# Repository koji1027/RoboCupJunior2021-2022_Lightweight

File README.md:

# RoboCupJunior2023_Lightweight
 高崎高校物理部 ロボカップジュニア2023 ライトウェイト部門

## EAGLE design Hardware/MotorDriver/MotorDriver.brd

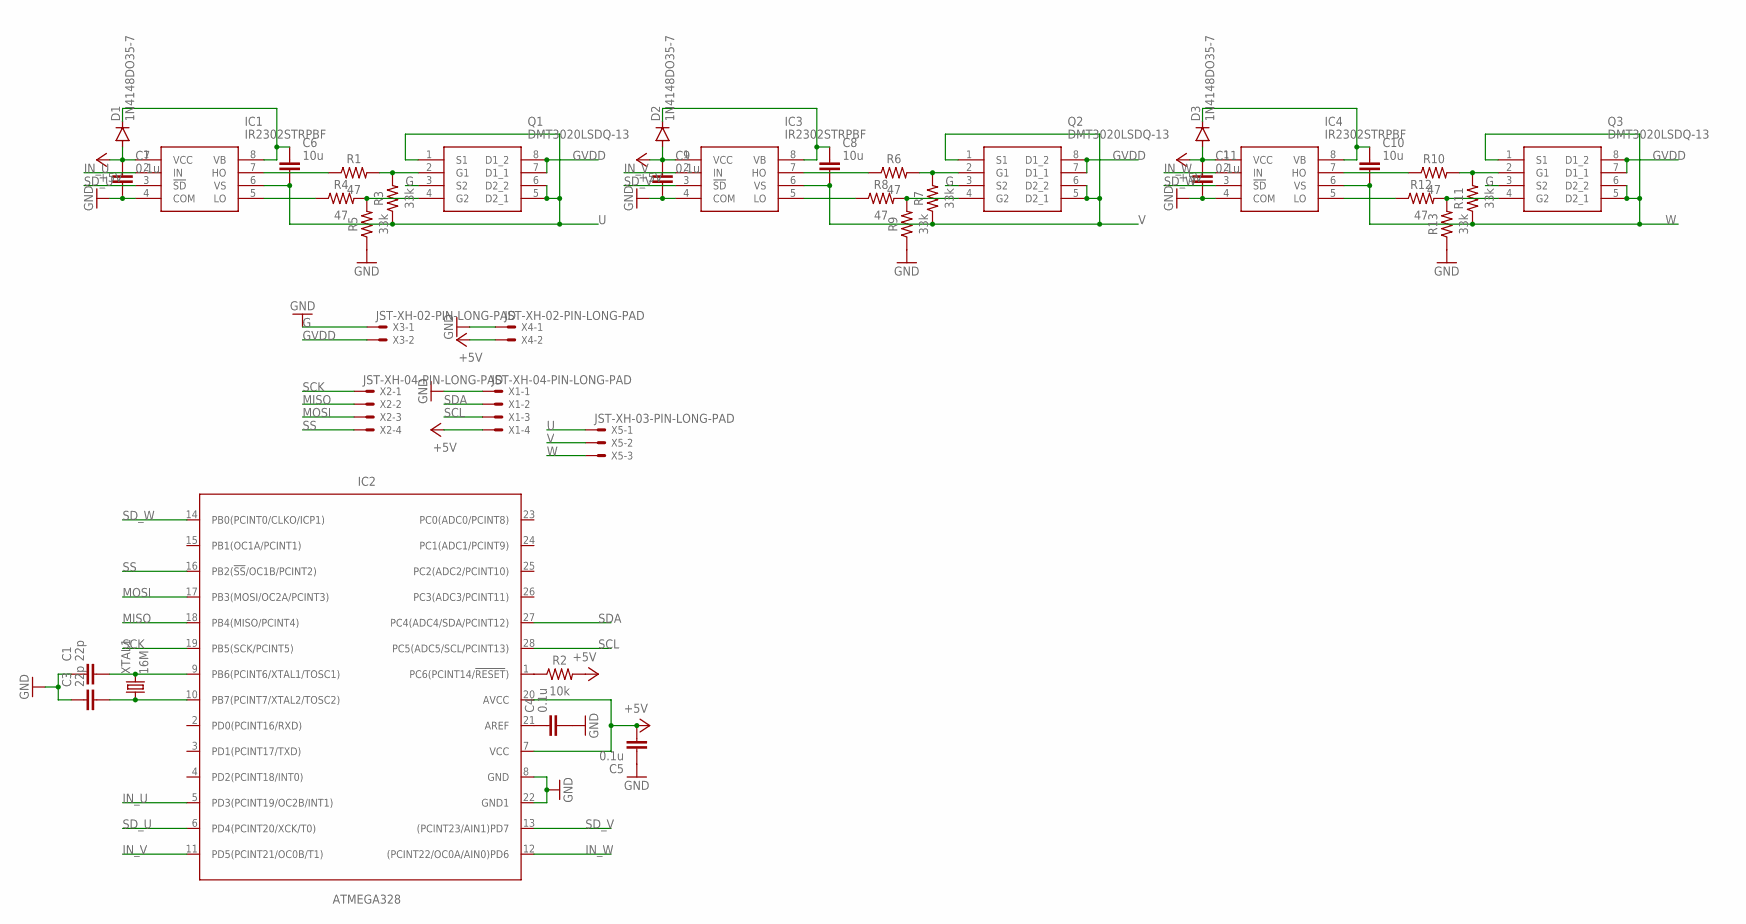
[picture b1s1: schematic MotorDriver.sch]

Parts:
C1, C3: 22p; CAPC1608X85
C4, C5, C7, C9, C11: 0.1u; CAPC1608X85
C6, C8, C10: 10u; CAPC1608X85
D1, D2, D3: 1N4148DO35-7; DO35-7
IC1, IC3, IC4: IR2302STRPBF; SOIC127P600X175-8N
IC2: ATMEGA328; DIP1016W53P254L3467H457Q28B
Q1, Q2, Q3: DMT3020LSDQ-13; SOIC127P600X170-8N
R1, R4, R6, R8, R10, R12: 47; RESC1608X60
R2: 10k; RESC1608X60
R3, R5, R7, R9, R11, R13: 33k; RESC1608X60
X1, X2: JST-XH-04-PIN-LONG-PAD; JST-XH-04-PACKAGE-LONG-PAD
X3, X4: JST-XH-02-PIN-LONG-PAD; JST-XH-02-PACKAGE-LONG-PAD
X5: JST-XH-03-PIN-LONG-PAD; JST-XH-03-PACKAGE-LONG-PAD
XTAL1: 16M; XTALRR488W45L1150T500H350B

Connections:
+5V: C5.2, C7.1, C9.1, C11.1, D1.A, D2.A, D3.A, IC1.1 (VCC), IC2.7 (VCC), IC2.20 (AVCC), IC3.1 (VCC), IC4.1 (VCC), R2.2, X1.4, X4.2
G: Q1.3 (S2), Q2.3 (S2), Q3.3 (S2), X3.1
GND: C1.1, C3.1, C4.2, C5.1, C7.2, C9.2, C11.2, IC1.4 (COM), IC2.8 (GND), IC2.22 (GND1), IC3.4 (COM), IC4.4 (COM), R5.1, R9.1, R13.1, X1.1, X4.1
GVDD: Q1.7 (D1_1), Q1.8 (D1_2), Q2.7 (D1_1), Q2.8 (D1_2), Q3.7 (D1_1), Q3.8 (D1_2), X3.2
IN_U: IC1.2 (IN), IC2.5 (PD3(PCINT19/OC2B/INT1))
IN_V: IC2.11 (PD5(PCINT21/OC0B/T1)), IC3.2 (IN)
IN_W: IC2.12 ((PCINT22/OC0A/AIN0)PD6), IC4.2 (IN)
MISO: IC2.18 (PB4(MISO/PCINT4)), X2.2
MOSI: IC2.17 (PB3(MOSI/OC2A/PCINT3)), X2.3
unnamed: C1.2, IC2.9 (PB6(PCINT6/XTAL1/TOSC1)), XTAL1.2
unnamed: C3.2, IC2.10 (PB7(PCINT7/XTAL2/TOSC2)), XTAL1.1
unnamed: IC2.1 (PC6(PCINT14/!RESET!)), R2.1
unnamed: C4.1, IC2.21 (AREF)
unnamed: C6.1, D1.C, IC1.8 (VB)
unnamed: IC1.7 (HO), R1.1
unnamed: Q1.2 (G1), R1.2, R3.2
unnamed: Q1.4 (G2), R4.2, R5.2
unnamed: IC1.5 (LO), R4.1
unnamed: C8.1, D2.C, IC3.8 (VB)
unnamed: IC3.7 (HO), R6.1
unnamed: Q2.2 (G1), R6.2, R7.2
unnamed: Q2.4 (G2), R8.2, R9.2
unnamed: IC3.5 (LO), R8.1
unnamed: C10.1, D3.C, IC4.8 (VB)
unnamed: IC4.7 (HO), R10.1
unnamed: Q3.2 (G1), R10.2, R11.2
unnamed: Q3.4 (G2), R12.2, R13.2
unnamed: IC4.5 (LO), R12.1
SCK: IC2.19 (PB5(SCK/PCINT5)), X2.1
SCL: IC2.28 (PC5(ADC5/SCL/PCINT13)), X1.3
SDA: IC2.27 (PC4(ADC4/SDA/PCINT12)), X1.2
SD_U: IC1.3 (!SD), IC2.6 (PD4(PCINT20/XCK/T0))
SD_V: IC2.13 ((PCINT23/AIN1)PD7), IC3.3 (!SD)
SD_W: IC2.14 (PB0(PCINT0/CLKO/ICP1)), IC4.3 (!SD)
SS: IC2.16 (PB2(!SS!/OC1B/PCINT2)), X2.4
U: C6.2, IC1.6 (VS), Q1.1 (S1), Q1.5 (D2_1), Q1.6 (D2_2), R3.1, X5.1
V: C8.2, IC3.6 (VS), Q2.1 (S1), Q2.5 (D2_1), Q2.6 (D2_2), R7.1, X5.2
W: C10.2, IC4.6 (VS), Q3.1 (S1), Q3.5 (D2_1), Q3.6 (D2_2), R11.1, X5.3

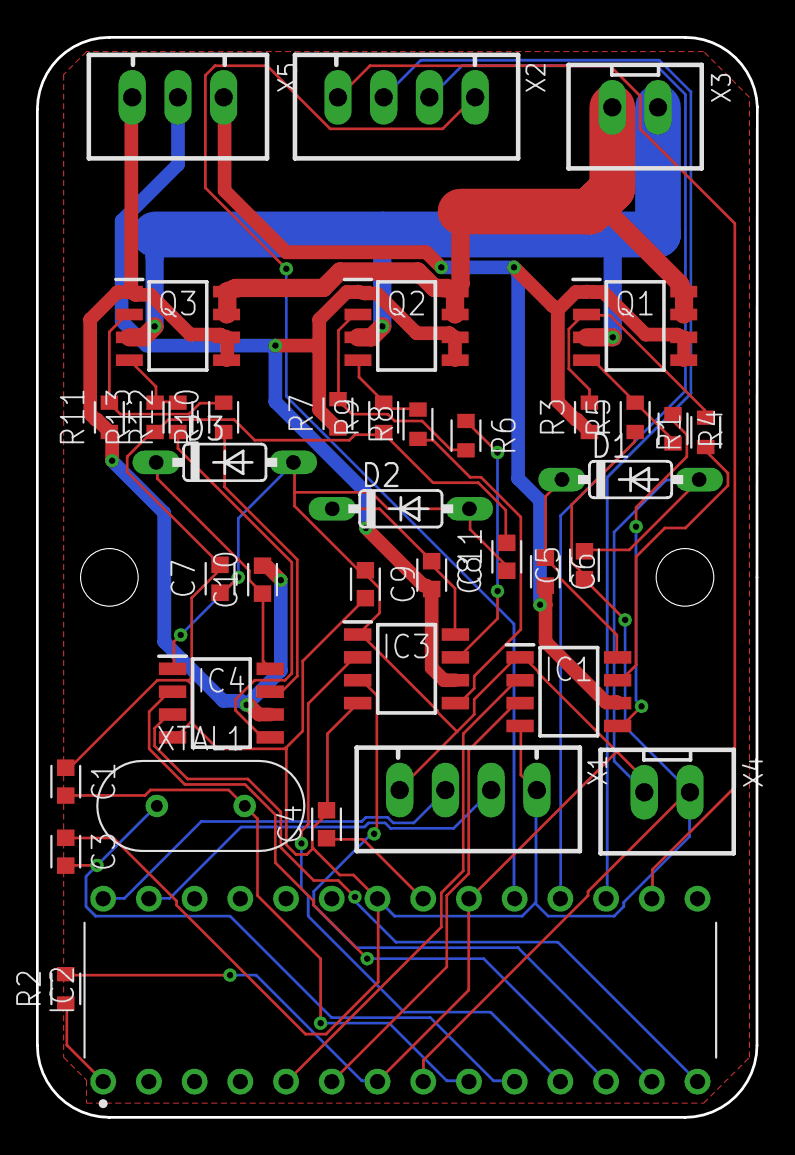
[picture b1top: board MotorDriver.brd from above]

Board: 2 copper layers, 40.0 x 60.0 mm, 39 parts (0 on the bottom side), 38 nets.

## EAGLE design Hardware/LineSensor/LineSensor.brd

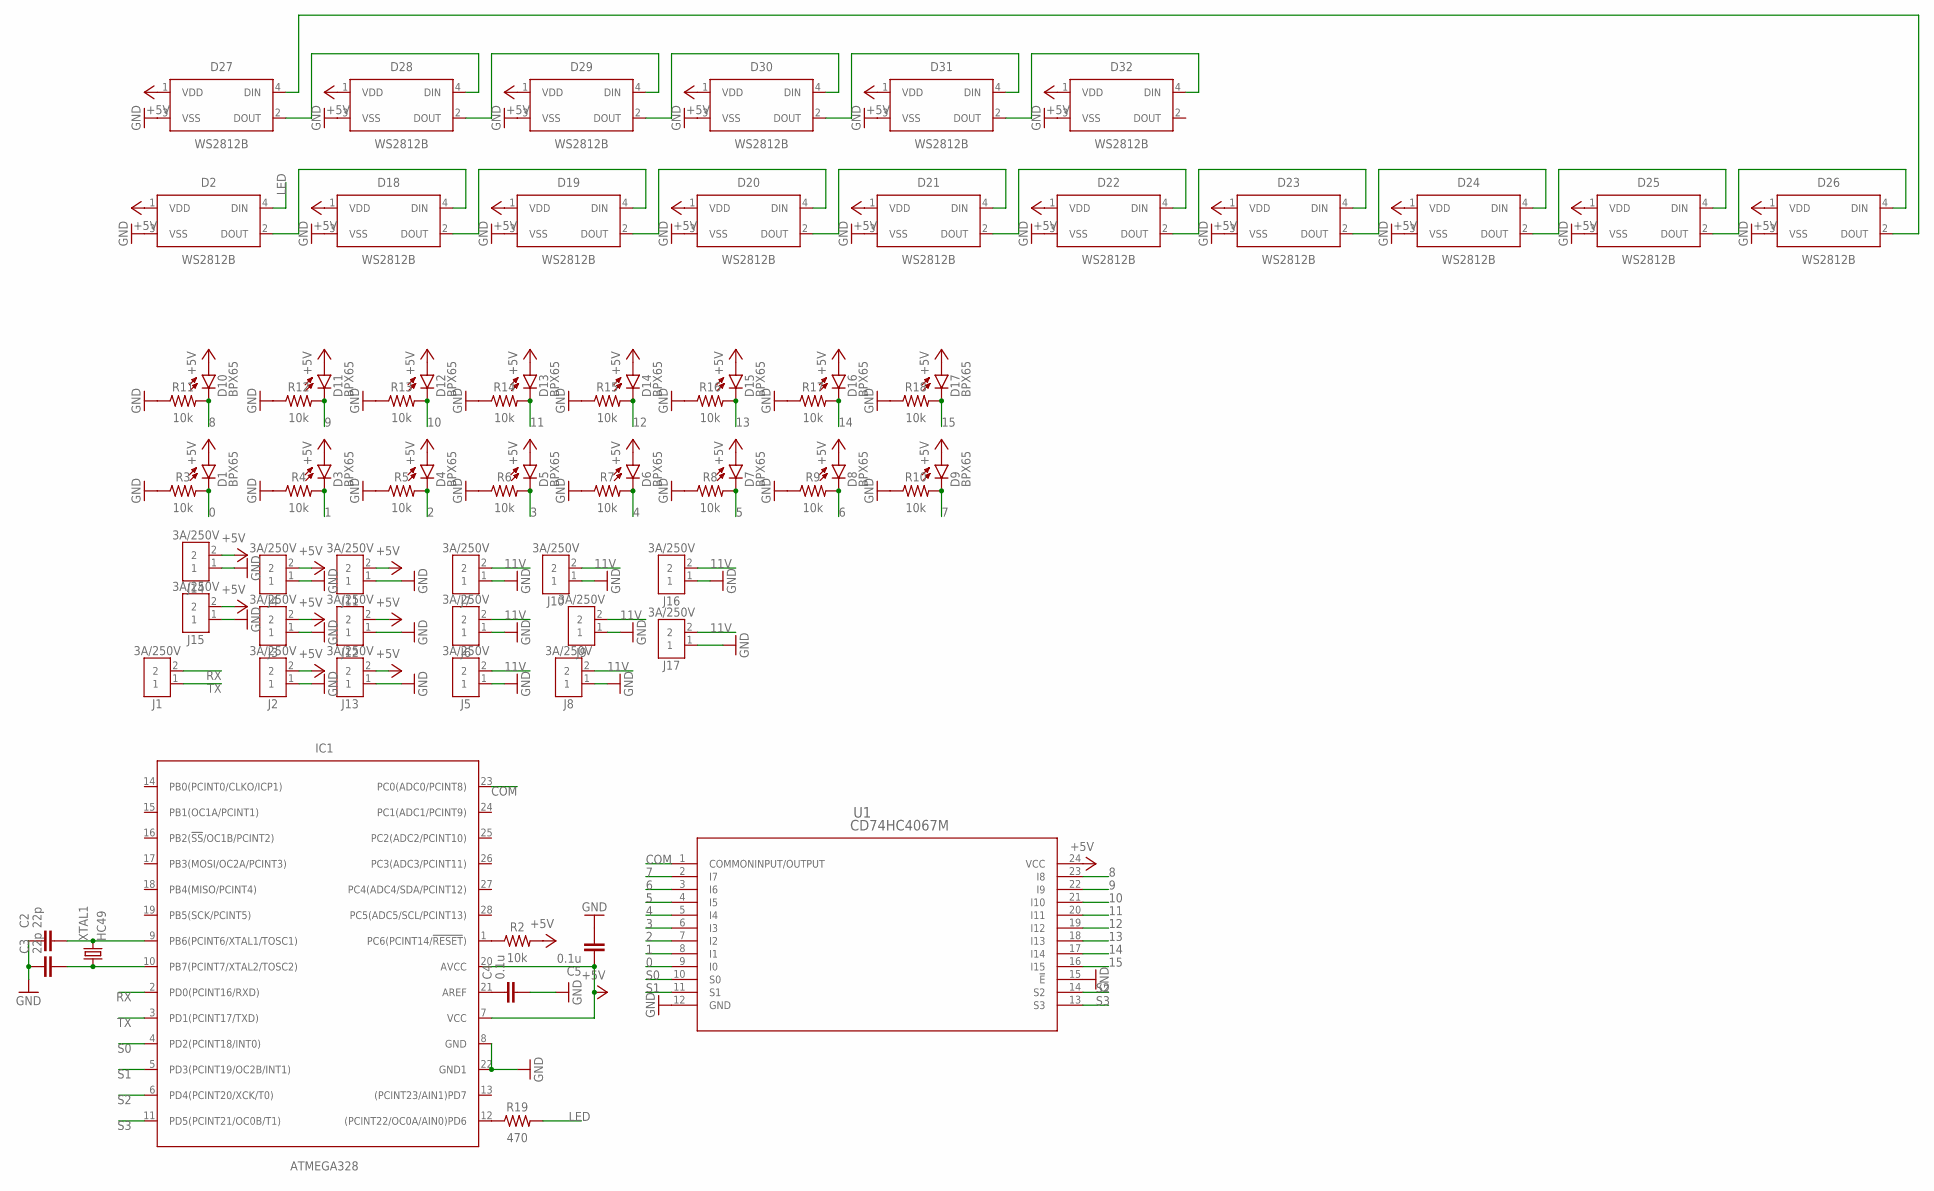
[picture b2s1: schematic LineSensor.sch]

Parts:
C2, C3: 22p; CAPC1608X85
C4, C5: 0.1u; CAPC1608X85
D1, D3, D4, D5, D6, D7, D8, D9, D10, D11, D12, D13, D14, D15, D16, D17: BPX65
D2, D18, D19, D20, D21, D22, D23, D24, D25, D26, D27, D28, D29, D30, D31, D32: WS2812B
IC1: ATMEGA328; DIP1016W53P254L3467H457Q28B
J1, J2, J3, J4, J5, J6, J7, J8, J9, J10, J11, J12, J13, J14, J15, J16, J17: 3A/250V; B2B-XH-A
R2, R3, R4, R5, R6, R7, R8, R9, R10, R11, R12, R13, R14, R15, R16, R17, R18: 10k; RESC1608X60
R19: 470; RESC1608X60
U1: CD74HC4067M; DW24
XTAL1: HC49; XTALRR488W45L1150T500H350B

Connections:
0: D1.K (C), R3.2, U1.9 (I0)
1: D3.K (C), R4.2, U1.8 (I1)
2: D4.K (C), R5.2, U1.7 (I2)
3: D5.K (C), R6.2, U1.6 (I3)
4: D6.K (C), R7.2, U1.5 (I4)
5: D7.K (C), R8.2, U1.4 (I5)
6: D8.K (C), R9.2, U1.3 (I6)
7: D9.K (C), R10.2, U1.2 (I7)
8: D10.K (C), R11.2, U1.23 (I8)
9: D11.K (C), R12.2, U1.22 (I9)
10: D12.K (C), R13.2, U1.21 (I10)
11: D13.K (C), R14.2, U1.20 (I11)
11V: J5.2, J6.2, J7.2, J8.2, J9.2, J10.2, J16.2, J17.2
12: D14.K (C), R15.2, U1.19 (I12)
13: D15.K (C), R16.2, U1.18 (I13)
14: D16.K (C), R17.2, U1.17 (I14)
15: D17.K (C), R18.2, U1.16 (I15)
+5V: C5.1, D1.A, D2.1 (VDD), D3.A, D4.A, D5.A, D6.A, D7.A, D8.A, D9.A, D10.A, D11.A, D12.A, D13.A, D14.A, D15.A, D16.A, D17.A, D18.1 (VDD), D19.1 (VDD), D20.1 (VDD), D21.1 (VDD), D22.1 (VDD), D23.1 (VDD), D24.1 (VDD), D25.1 (VDD), D26.1 (VDD), D27.1 (VDD), D28.1 (VDD), D29.1 (VDD), D30.1 (VDD), D31.1 (VDD), D32.1 (VDD), IC1.7 (VCC), IC1.20 (AVCC), J2.2, J3.2, J4.2, J11.2, J12.2, J13.2, J14.2, J15.2, R2.2, U1.24 (VCC)
COM: IC1.23 (PC0(ADC0/PCINT8)), U1.1 (COMMONINPUT/OUTPUT)
GND: C2.1, C3.1, C4.2, C5.2, D2.3 (VSS), D18.3 (VSS), D19.3 (VSS), D20.3 (VSS), D21.3 (VSS), D22.3 (VSS), D23.3 (VSS), D24.3 (VSS), D25.3 (VSS), D26.3 (VSS), D27.3 (VSS), D28.3 (VSS), D29.3 (VSS), D30.3 (VSS), D31.3 (VSS), D32.3 (VSS), IC1.8 (GND), IC1.22 (GND1), J2.1, J3.1, J4.1, J5.1, J6.1, J7.1, J8.1, J9.1, J10.1, J11.1, J12.1, J13.1, J14.1, J15.1, J16.1, J17.1, R3.1, R4.1, R5.1, R6.1, R7.1, R8.1, R9.1, R10.1, R11.1, R12.1, R13.1, R14.1, R15.1, R16.1, R17.1, R18.1, U1.12 (GND), U1.15 (!E)
LED: D2.4 (DIN), R19.2
unnamed: C2.2, IC1.9 (PB6(PCINT6/XTAL1/TOSC1)), XTAL1.2
unnamed: C3.2, IC1.10 (PB7(PCINT7/XTAL2/TOSC2)), XTAL1.1
unnamed: C4.1, IC1.21 (AREF)
unnamed: IC1.1 (PC6(PCINT14/!RESET!)), R2.1
unnamed: D2.2 (DOUT), D18.4 (DIN)
unnamed: D18.2 (DOUT), D19.4 (DIN)
unnamed: D19.2 (DOUT), D20.4 (DIN)
unnamed: D20.2 (DOUT), D21.4 (DIN)
unnamed: D21.2 (DOUT), D22.4 (DIN)
unnamed: D22.2 (DOUT), D23.4 (DIN)
unnamed: D23.2 (DOUT), D24.4 (DIN)
unnamed: D24.2 (DOUT), D25.4 (DIN)
unnamed: D25.2 (DOUT), D26.4 (DIN)
unnamed: D26.2 (DOUT), D27.4 (DIN)
unnamed: D27.2 (DOUT), D28.4 (DIN)
unnamed: D28.2 (DOUT), D29.4 (DIN)
unnamed: D29.2 (DOUT), D30.4 (DIN)
unnamed: D30.2 (DOUT), D31.4 (DIN)
unnamed: D31.2 (DOUT), D32.4 (DIN)
unnamed: IC1.12 ((PCINT22/OC0A/AIN0)PD6), R19.1
RX: IC1.2 (PD0(PCINT16/RXD)), J1.2
S0: IC1.4 (PD2(PCINT18/INT0)), U1.10 (S0)
S1: IC1.5 (PD3(PCINT19/OC2B/INT1)), U1.11 (S1)
S2: IC1.6 (PD4(PCINT20/XCK/T0)), U1.14 (S2)
S3: IC1.11 (PD5(PCINT21/OC0B/T1)), U1.13 (S3)
TX: IC1.3 (PD1(PCINT17/TXD)), J1.1

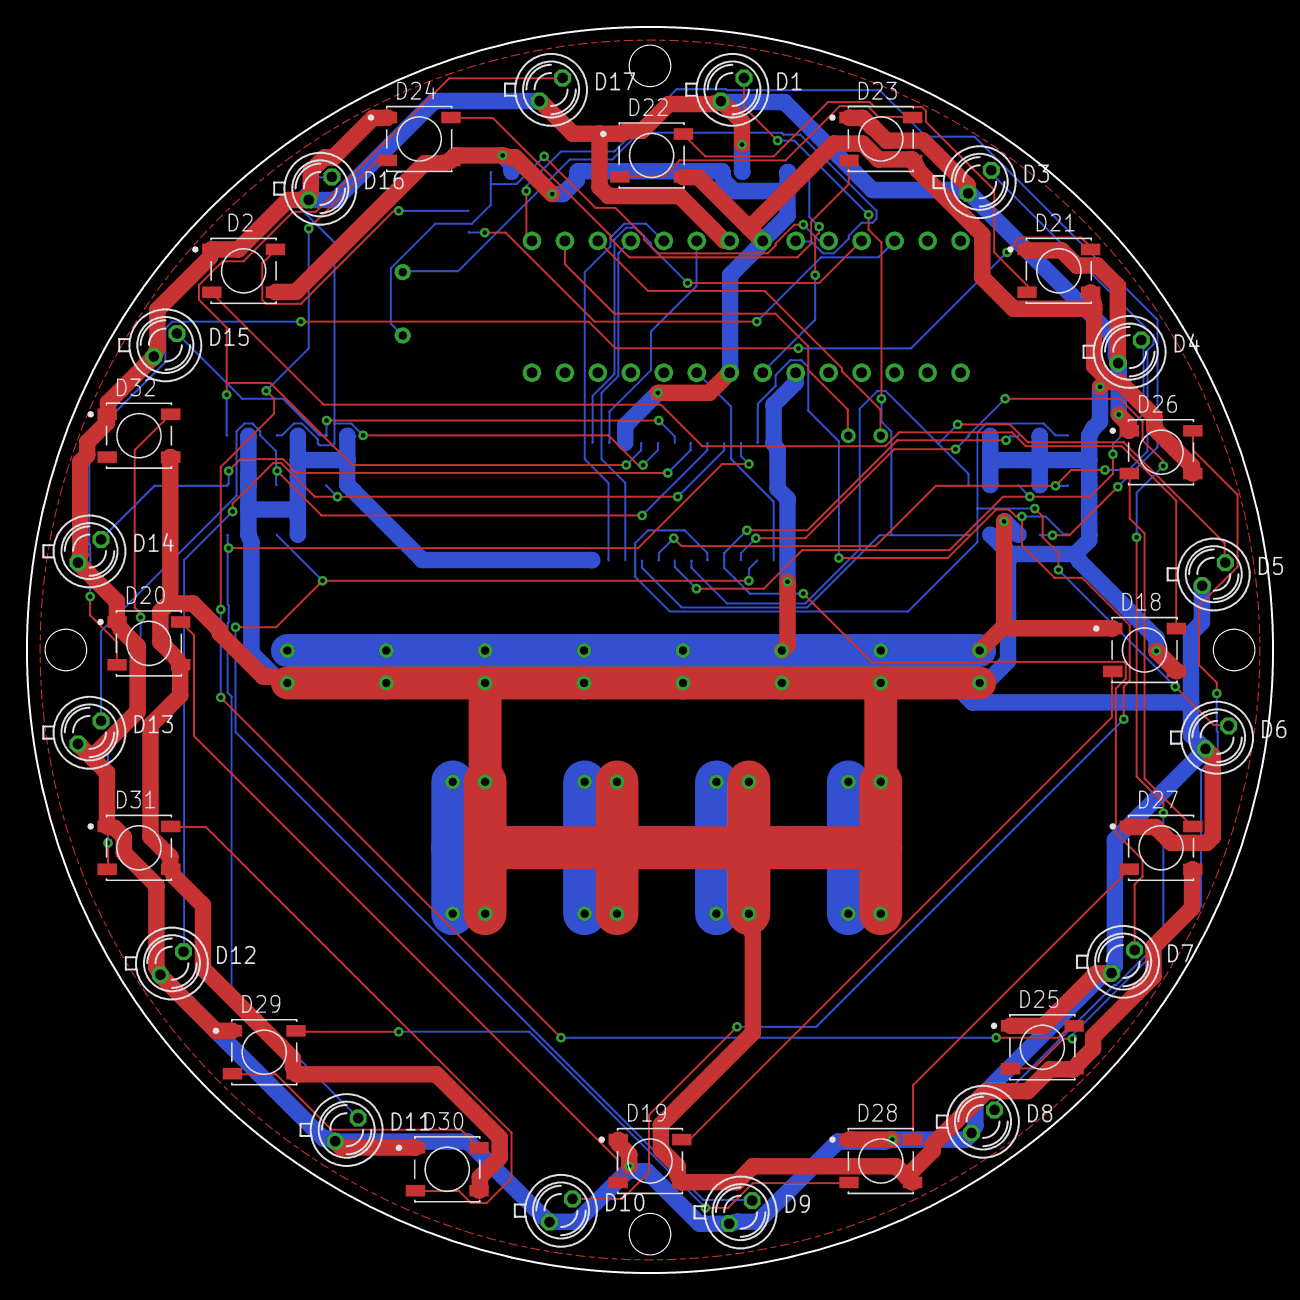
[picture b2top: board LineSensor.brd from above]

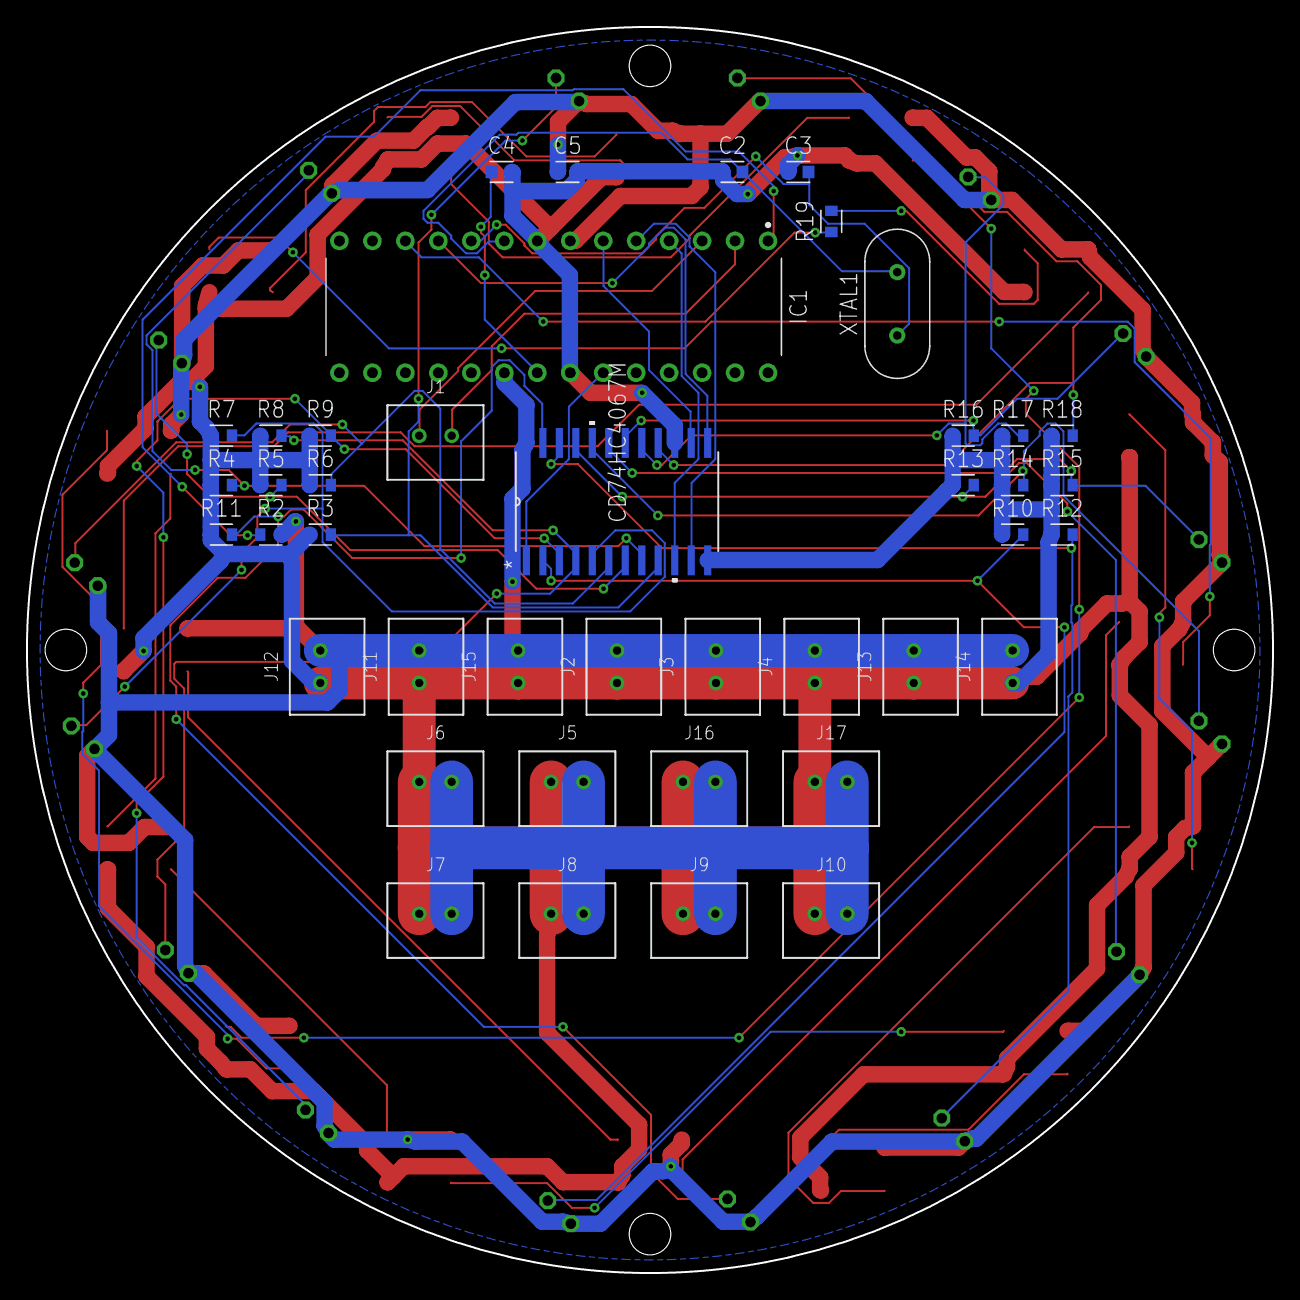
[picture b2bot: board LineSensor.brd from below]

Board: 2 copper layers, 96.0 x 96.0 mm, 74 parts (42 on the bottom side), 47 nets.

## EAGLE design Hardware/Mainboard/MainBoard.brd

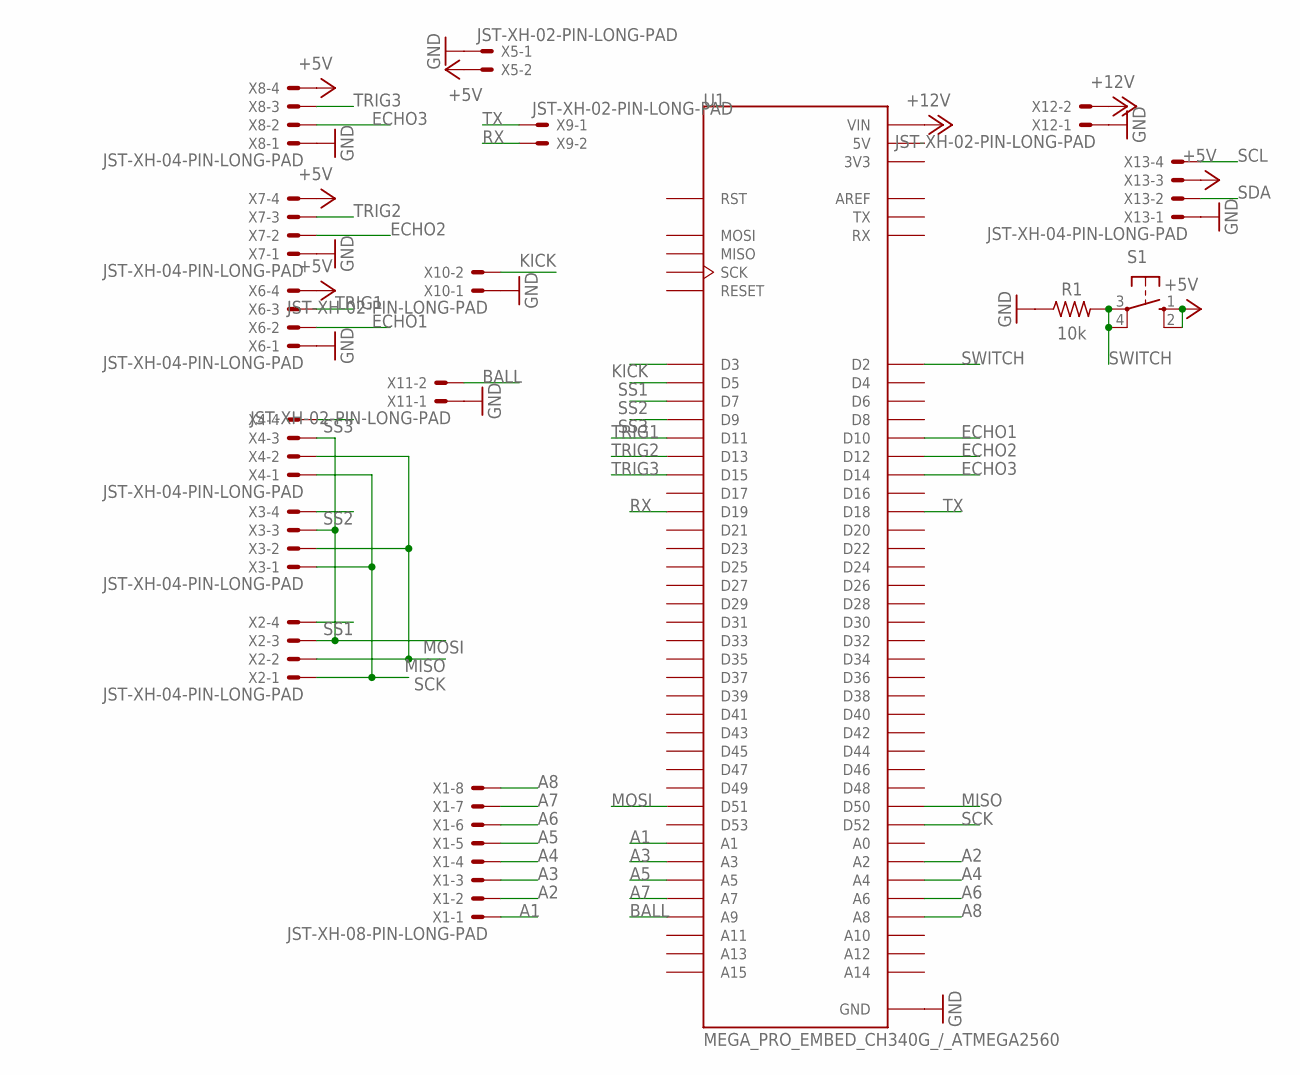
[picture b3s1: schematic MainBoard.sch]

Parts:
R1: 10k; RESC1608X60
S1: 10-XX; B3F-10XX
U1: MEGA_PRO_EMBED_CH340G_/_ATMEGA2560; MODULE_MEGA_PRO_EMBED_CH340G_/_ATMEGA2560
X1: JST-XH-08-PIN-LONG-PAD; JST-XH-08-PACKAGE-LONG-PAD
X2, X3, X4, X6, X7, X8, X13: JST-XH-04-PIN-LONG-PAD; JST-XH-04-PACKAGE-LONG-PAD
X5, X9, X10, X11, X12: JST-XH-02-PIN-LONG-PAD; JST-XH-02-PACKAGE-LONG-PAD

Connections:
3V3: U1.3V3_1 (3V3), U1.3V3_2 (3V3)
5V: U1.5V_1 (5V), U1.5V_2 (5V), U1.5V_3 (5V)
+5V: S1.1 (S), S1.2 (S1), X5.2, X6.4, X7.4, X8.4, X13.3
+12V: U1.VIN_1 (VIN), U1.VIN_2 (VIN), X12.2
A1: U1.A1, X1.1
A2: U1.A2, X1.2
A3: U1.A3, X1.3
A4: U1.A4, X1.4
A5: U1.A5, X1.5
A6: U1.A6, X1.6
A7: U1.A7, X1.7
A8: U1.A8, X1.8
BALL: U1.A9, X11.2
ECHO1: U1.D10, X6.2
ECHO2: U1.D12, X7.2
ECHO3: U1.D14, X8.2
GND: R1.1, U1.GND_1 (GND), U1.GND_2 (GND), U1.GND_3 (GND), X5.1, X6.1, X7.1, X8.1, X10.1, X11.1, X12.1, X13.1
KICK: U1.D3, X10.2
MISO: U1.D50, X2.2, X3.2, X4.2
MOSI: U1.D51, X2.3, X3.3, X4.3
RX: U1.D19, X9.2
SCK: U1.D52, X2.1, X3.1, X4.1
SCL: X13.4
SDA: X13.2
SS1: U1.D5, X2.4
SS2: U1.D7, X3.4
SS3: U1.D9, X4.4
SWITCH: R1.2, S1.3, S1.4 (P1), U1.D2
TRIG1: U1.D11, X6.3
TRIG2: U1.D13, X7.3
TRIG3: U1.D15, X8.3
TX: U1.D18, X9.1

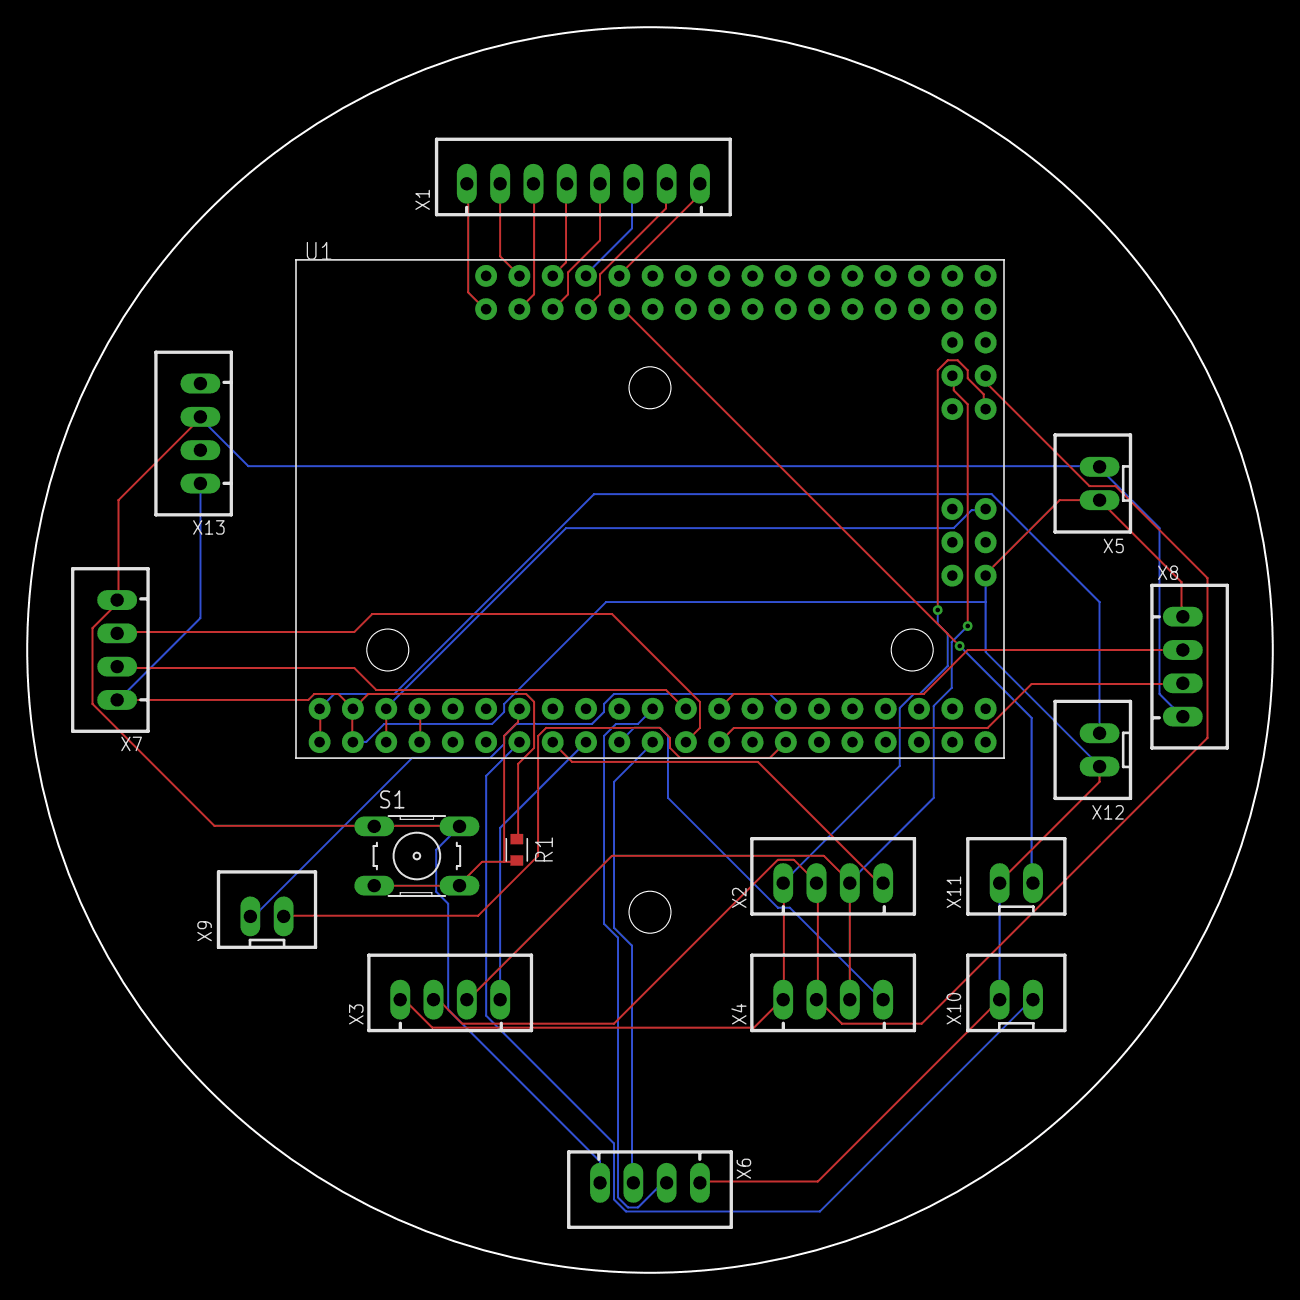
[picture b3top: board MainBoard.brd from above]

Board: 2 copper layers, 95.0 x 95.0 mm, 16 parts (0 on the bottom side), 30 nets.

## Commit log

2022-02-26 Magnetic Encorder PCB
    Magnetic Encorder PCB
2022-02-26 磁気式エンコーダ PCB基板
    磁気式エンコーダ PCB基板
2022-02-26 磁気式エンコーダ 3Dモデル
    磁気式エンコーダ 3Dモデル
2022-03-26 磁気式エンコーダ
2022-03-26 いろいろ
2022-03-26 いろいろ
    いろいろ
2022-04-04 やっと動いたやつ(BLDC)
    ああｌｆじせぎおえｗｊｇせｊふぉｒｗｋｐろｒｋｗくぉふぇおぎじじょｗじえりじょえｊごうぃｒじぇｊ

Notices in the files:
parts and their libraries:
COPYRIGHT: Copyright (C) 2022 Ultra Librarian. All rights reserved.
